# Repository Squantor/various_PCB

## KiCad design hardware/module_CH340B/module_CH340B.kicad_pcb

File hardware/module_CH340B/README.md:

# CH340B USB to serial converter module
This module converts USB to a FTDI style pinout serial uart, I/O voltage is fixed at 3.3V.
## TODO's
Still some things need to be done:
* schematic entry
* PCB layout
* Review with one night in between
* Produce at [OSHPARK](https://oshpark.com/)
* Assemble
* Test & characterise
* update Readme.md with pictures and BOM
## BOM
* [CH340B from LCSC](https://lcsc.com/product-detail/USB-ICs_WCH-Jiangsu-Qin-Heng-CH340B_C81010.html)
* [Low cost 3.3V regulator](https://lcsc.com/product-detail/Linear-Voltage-Regulators_HX-hengjiaxing-HX6206P332MR_C296230.html)

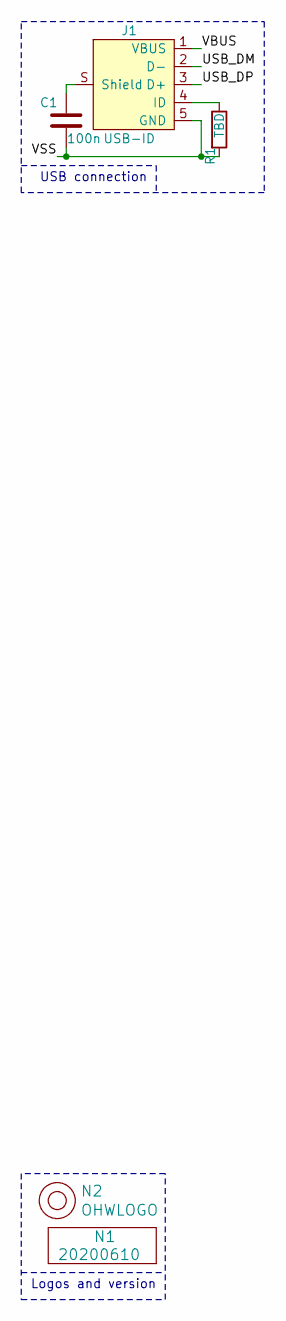
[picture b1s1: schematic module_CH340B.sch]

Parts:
C1: 100n; C_0805
J1: USB-ID; USB-muB-SMD_TH
N1: 20200610; Label_Generic
N2: OHWLOGO; OSHW-Symbol_6.7x6mm_SilkScreen
R1: TBD; R_0603_hand

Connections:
/USB_DM: J1.2 (D-)
/USB_DP: J1.3 (D+)
/VBUS: J1.1 (VBUS)
/VSS: C1.2, J1.5 (GND), R1.2
unnamed: C1.1, J1.S (Shield)
unnamed: J1.4 (ID), R1.1

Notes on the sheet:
Logos and version
USB connection

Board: 2 copper layers, 5 parts (0 on the bottom side), 3 nets, no tracks yet.

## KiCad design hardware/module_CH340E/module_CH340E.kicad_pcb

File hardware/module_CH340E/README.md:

# Jiangsu Qin Heng CH340E module
Module board for the [CH340E](http://www.wch.cn/product/CH340.html) USB to serial converter. Advantage of the CH340E is its compact size and low cost, requiring a minimum of additional components.
## TODO's
Still some things need to be done:
* schematic entry
* PCB layout
* Review with one night in between
* Produce at [OSHPARK](https://oshpark.com/)
* Assemble
* Test & characterise
* update Readme.md with pictures and BOM
## BOM
The CH340E is available from various chinese shops but can also be found on [LCSC](https://lcsc.com/).
* CH340E, [C99652 from LCSC](https://lcsc.com/product-detail/USB_CH340E_C99652.html)

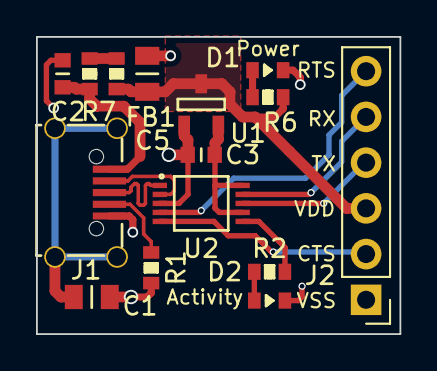
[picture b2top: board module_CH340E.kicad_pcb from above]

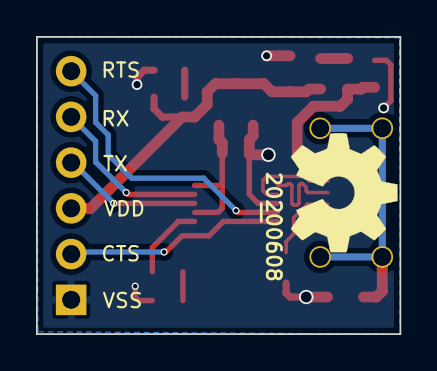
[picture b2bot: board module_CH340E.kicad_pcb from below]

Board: 2 copper layers, 20.2 x 16.5 mm, 17 parts (2 on the bottom side), 16 nets.

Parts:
C1: 100n; C_0805
C2: 100n; C_0603
C3: 1u; C_0603
C5: 10u; C_0805
D1: GRN; D_0603_hand
D2: RED; D_0603_hand
FB1: 600; R_0603_hand
J1: USB-ID; USB-muB-SMD_TH
J2: FTDI_PINS_1X06_input; PinHeader_1x06_P2.54mm_Vertical
N1: OHWLOGO; OSHW-Symbol_6.7x6mm_SilkScreen
N2: 20200608; Label_Generic
R1: 0; R_0603_hand
R2, R6: 1K; R_0603_hand
R7: Fuse; R_0603_hand
U1: MCP1702-CB; SOT23-3-Microchip-TT
U2: CH340E; MSOP-10

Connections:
/ACT: R2.2, U2.6
/CTSI: J2.2, U2.5
/RTSO: J2.6, U2.4
/RXI: J2.5, U2.9
/TXO: J2.4, U2.8
/USB_DM: J1.2, U2.2
/USB_DP: J1.3, U2.1
/V3: C3.2, U1.2, U2.7, U2.10
/VBUS: C2.1, J1.1, R7.2
/VDD: C5.1, FB1.1, J2.3, R6.2, U1.3
/VSS: C1.2, C2.2, C3.1, C5.2, D1.1, D2.1, J1.5, J2.1, R1.2, U1.1, U2.3
unnamed: C1.1, J1.S
unnamed: D1.2, R6.1
unnamed: D2.2, R2.1
unnamed: FB1.2, R7.1
unnamed: J1.4, R1.1

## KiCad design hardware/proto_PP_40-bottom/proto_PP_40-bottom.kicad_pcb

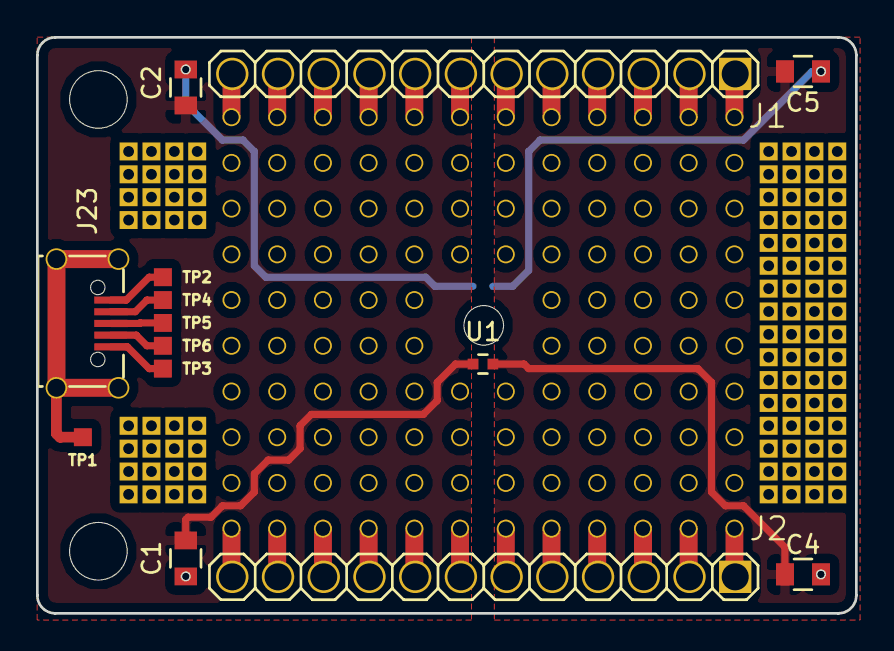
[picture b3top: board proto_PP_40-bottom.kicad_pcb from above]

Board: 2 copper layers, 45.5 x 32.0 mm, 37 parts (1 on the bottom side), 34 nets.

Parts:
C1, C2, C4, C5: C; C_0805
H1, H2: Drill_Hole_no_metal; MountingHole_3.2mm_no_metal
H3: Drill_Hole_no_metal; MountingHole_2.2mm_no_metal
J1, J2: PINS_1X12; Header-0254-1X12-H015
J3, J4, J16, J19: Proto; proto-TH-0254-04X04-P010SQ-H008
J5, J6: Proto; proto-TH-0254-04X04-GAP02-P010SQ-H008
J7, J8, J9, J10, J11, J12: Proto_4pins; proto-TH-0254-04X01-P010SQ-H008
J13, J14, J17, J20, J21, J22: Proto; proto-SMD-0127-04X04-P010-H006
J23: USB-ID; SquantorUsb-USB-UB-SMD4H
N2: V20171123; Label_version
TP1, TP2, TP3, TP4, TP5, TP6: testpad; TESTPAD_SQ_1MM
U1, U2: POWER_JOINER; R_0402_hand

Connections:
GND: C1.2, C2.2, U2.1
GNDA: C4.2, C5.2, U2.2
unnamed: J1.1, J7.1
unnamed: J1.2, J7.2
unnamed: J1.3, J7.3
unnamed: J1.4, J7.4
unnamed: J1.5, J9.1
unnamed: J1.6, J9.2
unnamed: J1.7, J9.3
unnamed: J1.8, J9.4
unnamed: J1.9, J8.1
unnamed: J1.10, J8.2
unnamed: J1.11, J8.3
unnamed: J1.12, J8.4
unnamed: J2.5, J10.1
unnamed: J2.6, J10.2
unnamed: J2.7, J10.3
unnamed: J2.8, J10.4
unnamed: J2.1, J11.1
unnamed: J2.2, J11.2
unnamed: J2.3, J11.3
unnamed: J2.4, J11.4
unnamed: J2.9, J12.1
unnamed: J2.10, J12.2
unnamed: J2.11, J12.3
unnamed: J2.12, J12.4
unnamed: J23.1, TP2.1
unnamed: J23.2, TP4.1
unnamed: J23.3, TP5.1
unnamed: J23.4, TP6.1
unnamed: J23.5, TP3.1
unnamed: J23.S, TP1.1
VDD: C1.1, C2.1, U1.1
VDDA: C4.1, C5.1, U1.2

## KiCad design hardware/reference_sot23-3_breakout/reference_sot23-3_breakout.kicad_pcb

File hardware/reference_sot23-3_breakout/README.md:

# SOT23 3 pin reference breakout
Most SOT23 references have the same pinout, this breakout accomodates these references. These include the MCP1525 and various linear reference chips.
## TODO's
Still some things need to be done:
* Produce at [OSHPARK](https://oshpark.com/shared_projects/Y7oW3KIf) (WIP)
* Assemble (TODO)
* Test & characterise (TODO)
* update Readme.md with pictures and BOM (TODO)
## BOM
Due to the general shortage of passive components, where mentioned, just whatever you can find.
* Any 3 pin SOT23 references (do check pinout naturally)
* footprints available for capacitors in 0805 and 0603

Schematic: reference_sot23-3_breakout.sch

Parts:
C1, C2: TBD; C_0805+0603
J1: reference_output
J2: reference_input
N1: OHWLOGO; OSHW-Symbol_6.7x6mm_SilkScreen
N2: 20190505; Label_version
U1: reference3pin; SOT23-3-Microchip-TT

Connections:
/VIN: C1.1, J2.1, J2.2, U1.1 (VIN)
/VOUT: C2.1, J1.3, J1.4, U1.2 (VOUT)
/VSS: C1.2, C2.2, J1.1, J1.2, J2.3, J2.4, U1.3 (VSS)

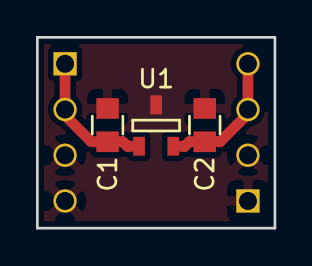
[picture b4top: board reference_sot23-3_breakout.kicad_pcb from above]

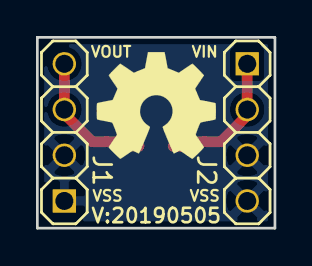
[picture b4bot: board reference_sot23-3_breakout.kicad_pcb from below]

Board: 2 copper layers, 13.2 x 10.6 mm, 7 parts (3 on the bottom side), 3 nets.

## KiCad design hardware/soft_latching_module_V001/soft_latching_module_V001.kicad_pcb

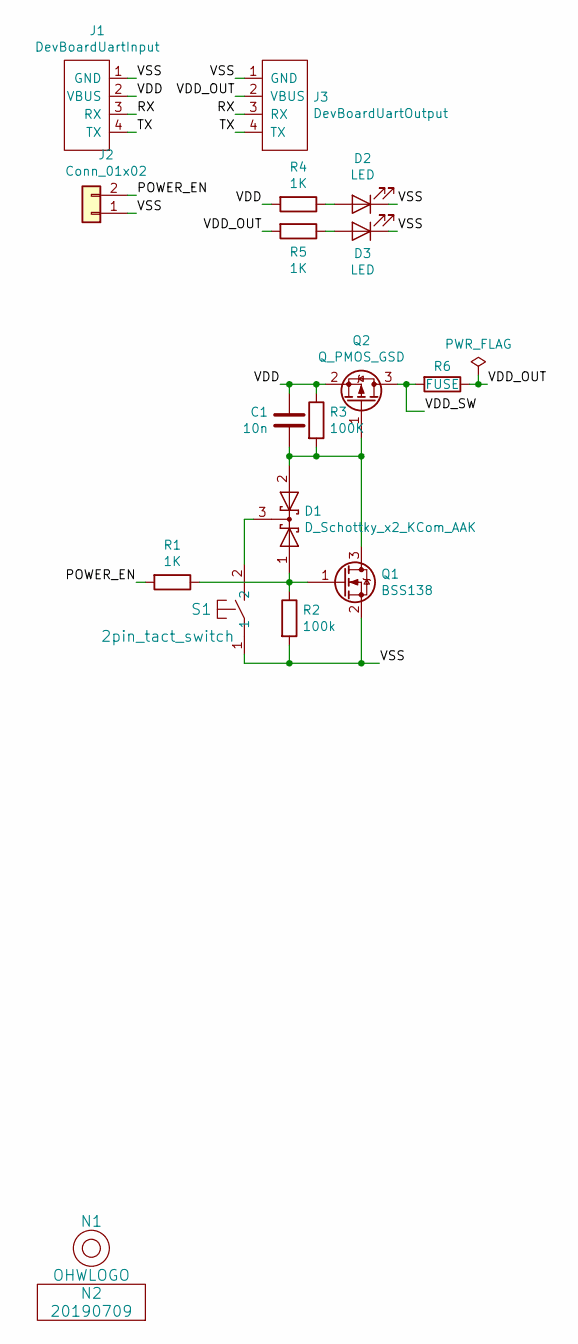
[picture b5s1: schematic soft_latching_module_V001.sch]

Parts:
C1: 10n; C_0603
D1: D_Schottky_x2_KCom_AAK; SOT23-3
D2, D3: LED; LED_0603_hand
J1: DevBoardUartInput; JST_PH_S4B-PH-K_1x04_P2.00mm_Horizontal
J2: Conn_01x02; JST_PH_S2B-PH-K_1x02_P2.00mm_Horizontal
J3: DevBoardUartOutput; JST_PH_S4B-PH-K_1x04_P2.00mm_Horizontal
N1: OHWLOGO; OSHW-Symbol_6.7x6mm_SilkScreen
N2: 20190709; Label_version
Q1: BSS138; SOT23-3
Q2: Q_PMOS_GSD; SOT23-3
R1, R4, R5: 1K; R_0603_hand
R2: 100k; R_0603_hand
R3: 100K; R_0603_hand
R6: FUSE; R_0603_hand
S1: 2pin_tact_switch; DTSM3

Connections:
/POWER_EN: J2.2, R1.2
/RX: J1.3 (RX), J3.3 (RX)
/TX: J1.4 (TX), J3.4 (TX)
/VDD: C1.1, J1.2 (VBUS), Q2.2 (S), R3.1, R4.2
/VDD_OUT: J3.2 (VBUS), R5.2, R6.1
/VDD_SW: Q2.3 (D), R6.2
/VSS: D2.1 (K), D3.1 (K), J1.1 (GND), J2.1, J3.1 (GND), Q1.2 (S), R2.2, S1.1
unnamed: C1.2, D1.2 (A), Q1.3 (D), Q2.1 (G), R3.2
unnamed: D1.1 (A), Q1.1 (G), R1.1, R2.1
unnamed: D1.3 (K), S1.2
unnamed: D2.2 (A), R4.1
unnamed: D3.2 (A), R5.1

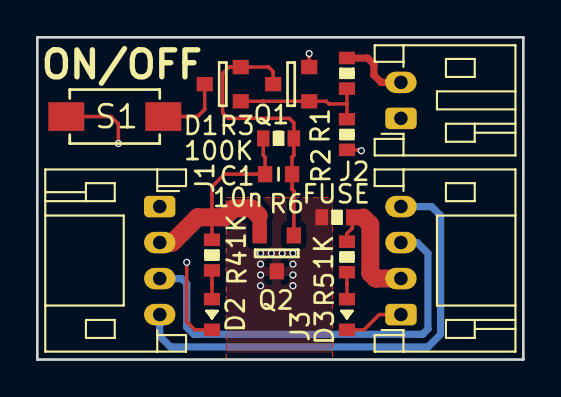
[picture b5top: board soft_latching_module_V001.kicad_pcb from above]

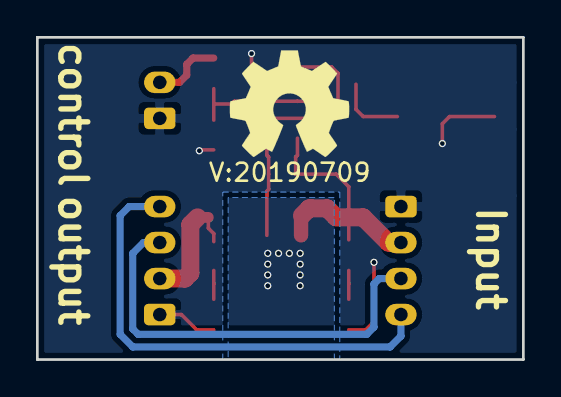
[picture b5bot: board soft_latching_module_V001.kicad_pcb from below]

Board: 2 copper layers, 27.0 x 17.9 mm, 18 parts (2 on the bottom side), 12 nets.

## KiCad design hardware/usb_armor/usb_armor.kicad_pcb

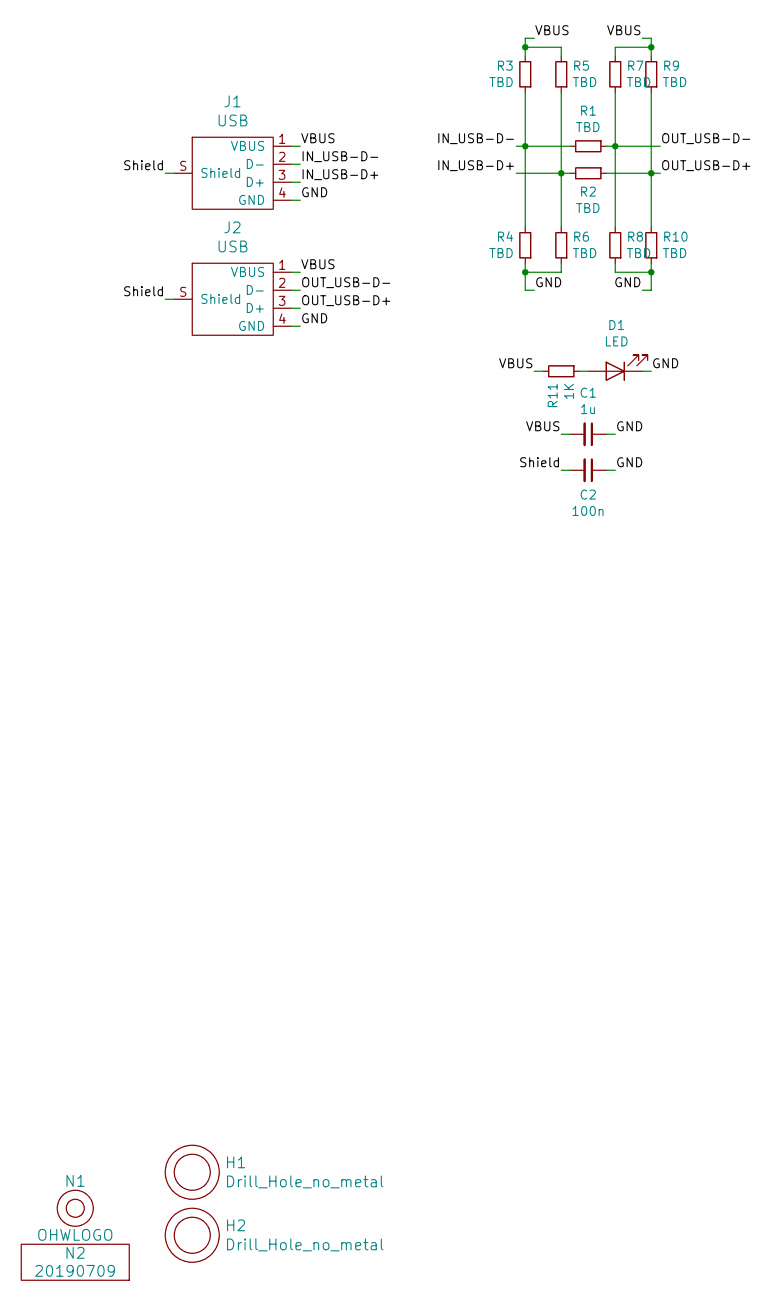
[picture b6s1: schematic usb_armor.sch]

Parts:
C1: 1u; C_0805
C2: 100n; C_0805
D1: LED; LED_D3.0mm
H1, H2: Drill_Hole_no_metal; MountingHole_2.5mm_no_metal
J1: USB; USB_A-Plug-generic
J2: USB; USB-A-TH
N1: OHWLOGO; OSHW-Symbol_6.7x6mm_SilkScreen
N2: 20190709; Label_version
R1, R2, R3, R4, R5, R6, R7, R8, R9, R10: TBD; R_0603_hand
R11: 1K; R_0603_hand

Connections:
/GND: C1.1, C2.1, D1.1 (K), J1.4 (GND), J2.4 (GND), R4.1, R6.1, R8.1, R10.1
/IN_USB-D+: J1.3 (D+), R2.2, R5.1, R6.2
/IN_USB-D-: J1.2 (D-), R1.2, R3.1, R4.2
/OUT_USB-D+: J2.3 (D+), R2.1, R9.1, R10.2
/OUT_USB-D-: J2.2 (D-), R1.1, R7.1, R8.2
/Shield: C2.2, J1.S (Shield), J2.S (Shield)
/VBUS: C1.2, J1.1 (VBUS), J2.1 (VBUS), R3.2, R5.2, R7.2, R9.2, R11.2
unnamed: D1.2 (A), R11.1

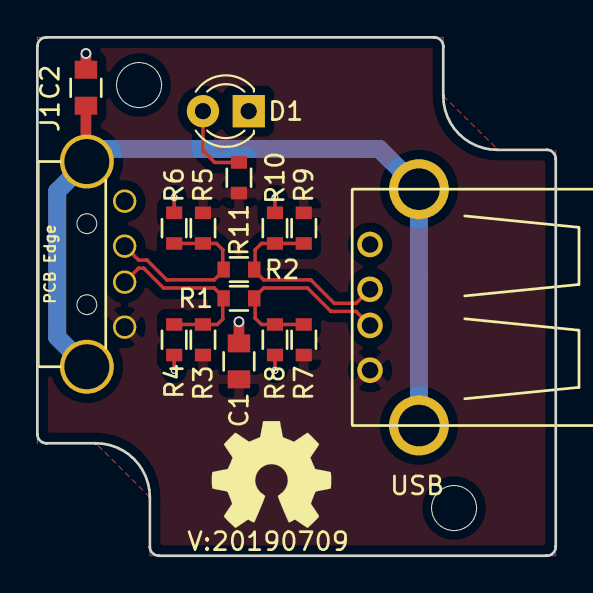
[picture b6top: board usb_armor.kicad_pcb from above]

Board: 2 copper layers, 28.8 x 28.8 mm, 20 parts (0 on the bottom side), 8 nets.
